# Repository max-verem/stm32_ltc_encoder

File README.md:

# stm32_ltc_encoder

This device used for decoding/encoding LTC (EBU Linear timecode) from/to VTRs or other sources.

Decoded Output sent to CDC serial. Encoding control cli available on second CDC serial.

## schematic

## photo

## encoding/generating LTC

## decoding LTC

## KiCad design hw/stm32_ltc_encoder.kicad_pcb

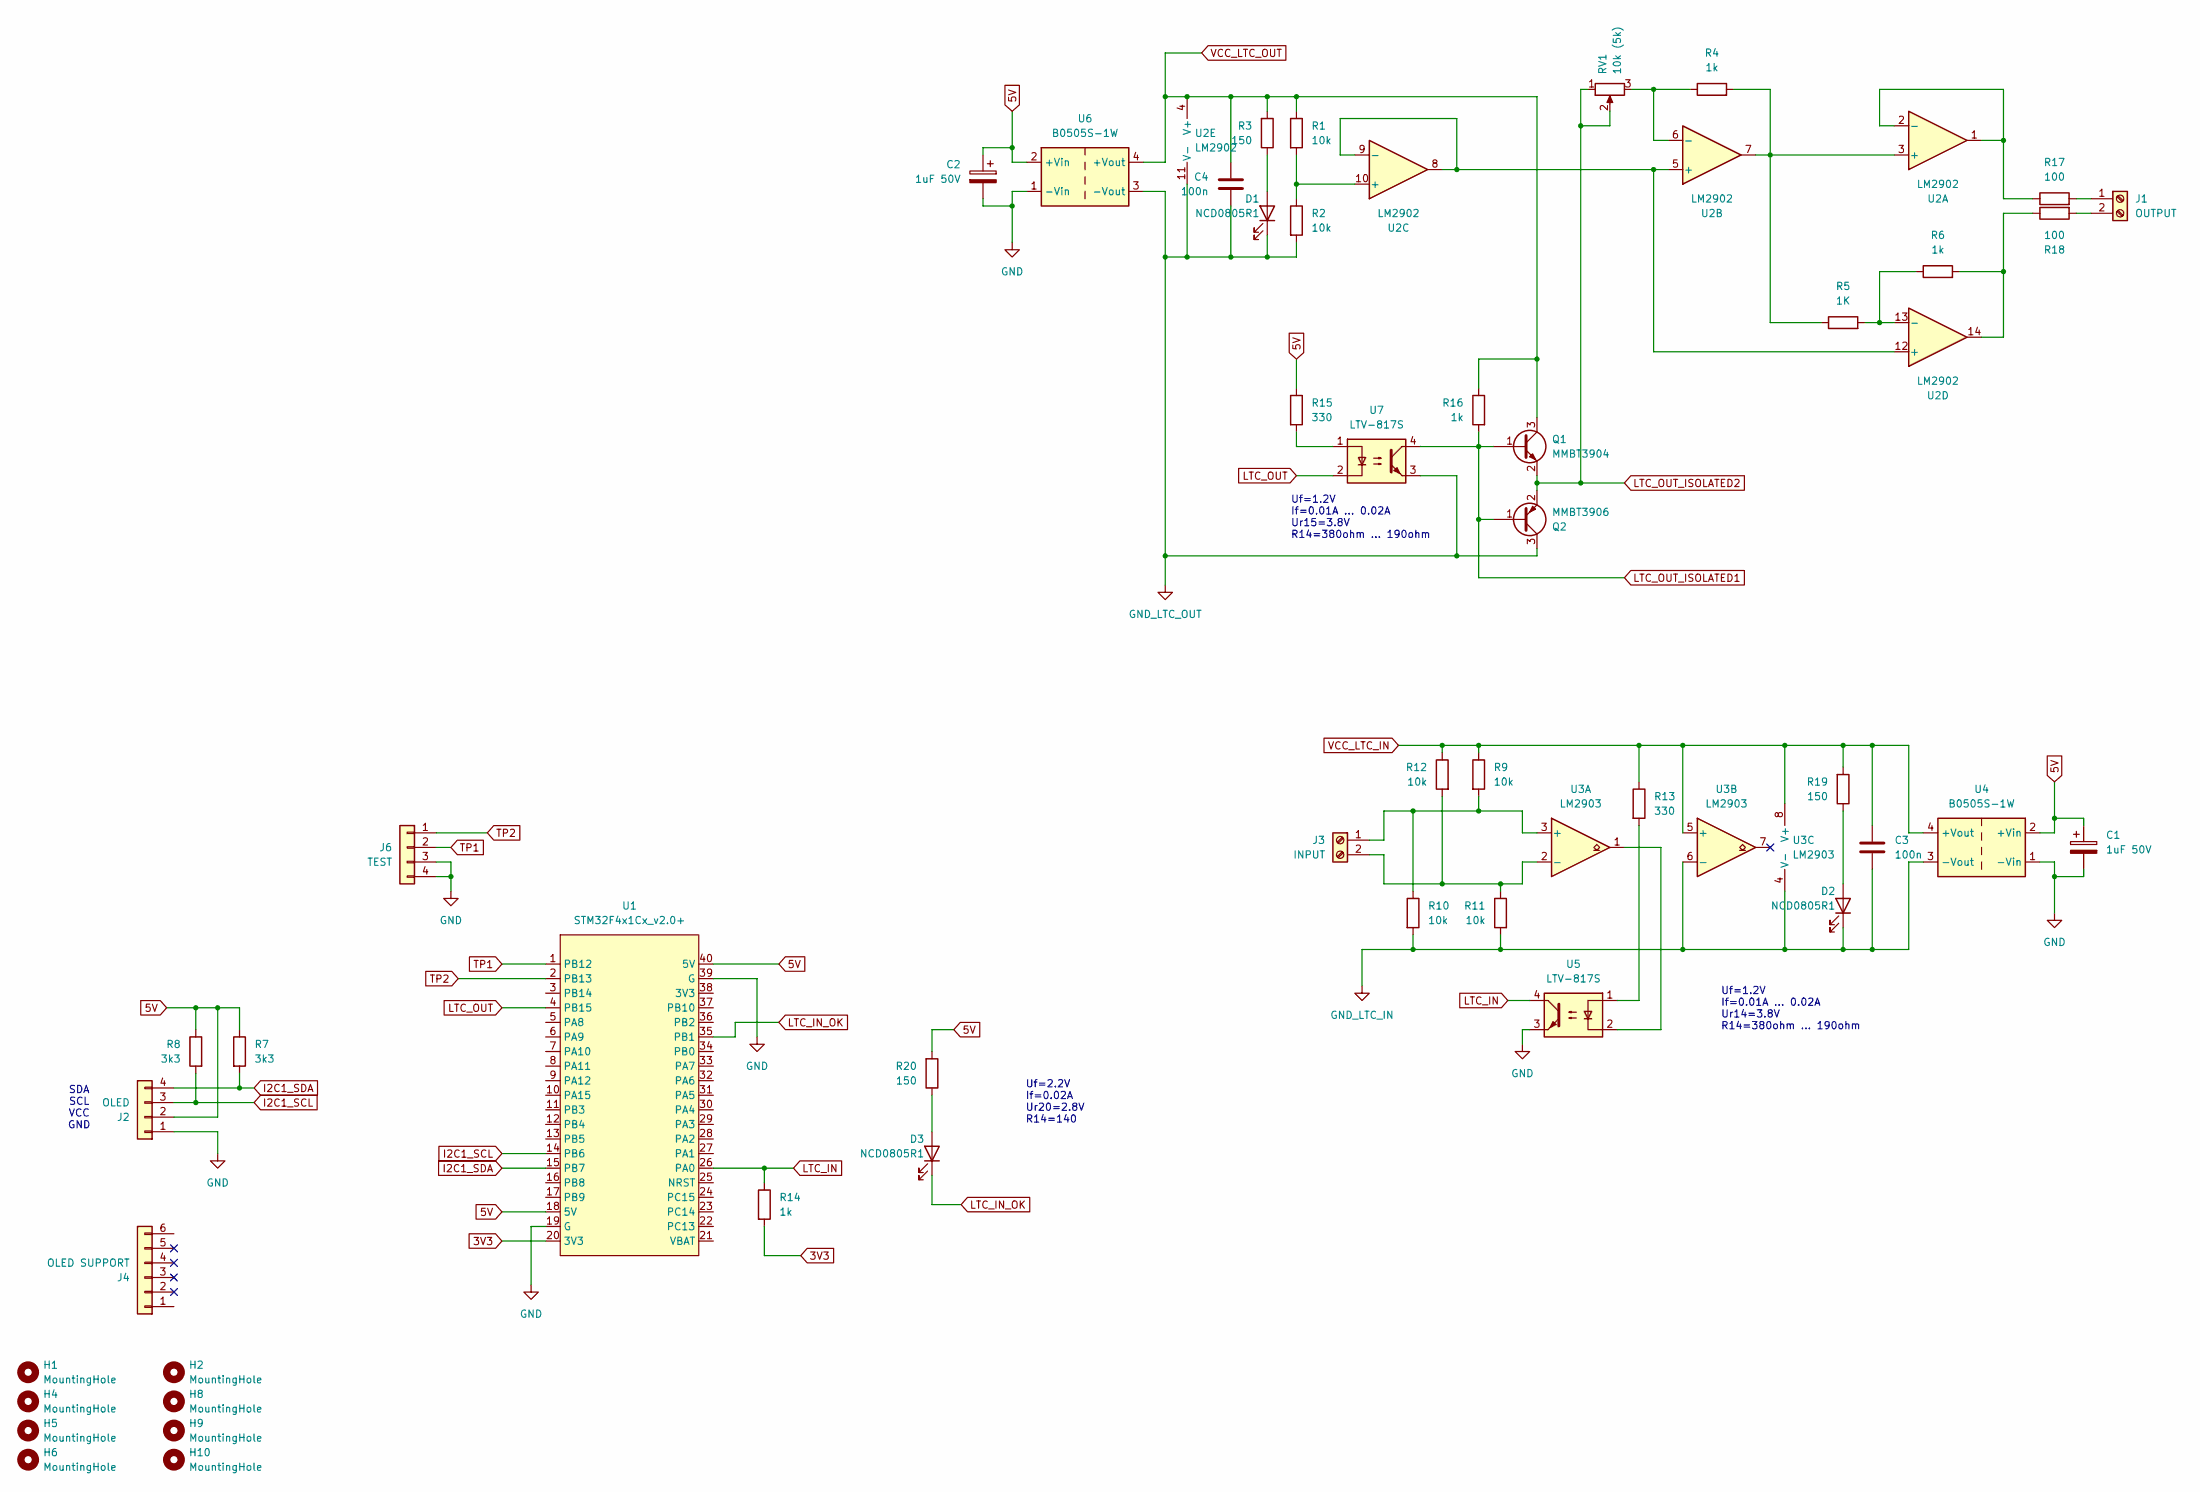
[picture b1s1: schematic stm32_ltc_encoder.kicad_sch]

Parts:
C1, C2: 1uF 50V; C_0805_2012Metric_Pad1.18x1.45mm_HandSolder
C3, C4: 100n; C_0805_2012Metric_Pad1.18x1.45mm_HandSolder
D1, D2, D3: NCD0805R1; LED_0805_2012Metric; JLCPCB Part # C84256
H1, H2, H4, H5, H6, H8, H9, H10: MountingHole; MountingHole_3.2mm_M3
J1: OUTPUT; TerminalBlock_bornier-2_P5.08mm; JLCPCB Part # C557646
J2: OLED; PinHeader_1x04_P2.54mm_Vertical
J3: INPUT; TerminalBlock_bornier-2_P5.08mm; JLCPCB Part # C557646
J4: OLED SUPPORT; PinHeader_1x06_P2.54mm_Vertical
J6: TEST; PinHeader_1x04_P2.54mm_Vertical
Q1: MMBT3904; SOT-23
Q2: MMBT3906; SOT-23
R1, R2, R9, R10, R11, R12: 10k; R_0805_2012Metric_Pad1.20x1.40mm_HandSolder
R3, R19, R20: 150; R_0805_2012Metric; JLCPCB Part # C17714
R4, R6, R14, R16: 1k; R_0805_2012Metric_Pad1.20x1.40mm_HandSolder
R5: 1K; R_0805_2012Metric_Pad1.20x1.40mm_HandSolder
R7, R8: 3k3; R_0805_2012Metric_Pad1.20x1.40mm_HandSolder
R13, R15: 330; R_0805_2012Metric_Pad1.20x1.40mm_HandSolder
R17, R18: 100; R_0805_2012Metric_Pad1.20x1.40mm_HandSolder
RV1: 10k (5k); Potentiometer_Bourns_3266W_Vertical
U1: STM32F4x1Cx_v2.0+; DIP-40_W15.24mm_LongPads
U2: LM2902; SOIC-14_3.9x8.7mm_P1.27mm
U3: LM2903; SOIC-8_3.9x4.9mm_P1.27mm
U4, U6: B0505S-1W; Converter_DCDC_TRACO_TME_03xxS_05xxS_12xxS_Single_THT
U5, U7: LTV-817S; SMDIP-4_W9.53mm

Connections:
3V3: R14.2, U1.20 (3V3)
5V: C1.1, C2.1, J2.2, R7.1, R8.1, R15.1, R20.2, U1.18 (5V), U1.40 (5V), U4.2 (+Vin), U6.2 (+Vin)
GND: C1.2, C2.2, J2.1, J6.3, J6.4, U1.19 (G), U1.39 (G), U4.1 (-Vin), U5.3, U6.1 (-Vin)
GND_LTC_IN: C3.2, D2.1 (K), R10.2, R11.2, U3.4 (V-), U3.6 (-), U4.3 (-Vout)
GND_LTC_OUT: C4.2, D1.1 (K), Q2.3 (C), R2.2, U2.11 (V-), U6.3 (-Vout), U7.3
I2C1_SCL: J2.3, R8.2, U1.14 (PB6)
I2C1_SDA: J2.4, R7.2, U1.15 (PB7)
LTC_IN: R14.1, U1.26 (PA0), U5.4
LTC_IN_OK: D3.1 (K), U1.35 (PB1)
LTC_OUT: U1.4 (PB15), U7.2
LTC_OUT_ISOLATED1: Q1.1 (B), Q2.1 (B), R16.2, U7.4
LTC_OUT_ISOLATED2: Q1.2 (E), Q2.2 (E), RV1.1, RV1.2
unnamed: D1.2 (A), R3.1
unnamed: D2.2 (A), R19.1
unnamed: D3.2 (A), R20.1
unnamed: J1.1, R17.2
unnamed: J1.2, R18.2
unnamed: J3.1, R9.2, R10.1, U3.3 (+)
unnamed: J3.2, R11.1, R12.2, U3.2 (-)
unnamed: R13.2, U5.1
unnamed: R15.2, U7.1
unnamed: R6.2, R18.1, U2.14
unnamed: R4.2, R5.1, U2.3 (+), U2.7
unnamed: R17.1, U2.1, U2.2 (-)
unnamed: U2.5 (+), U2.8, U2.9 (-), U2.12 (+)
unnamed: R4.1, RV1.3, U2.6 (-)
unnamed: R1.2, R2.1, U2.10 (+)
unnamed: R5.2, R6.1, U2.13 (-)
unnamed: U3.1, U5.2
TP1: J6.2, U1.1 (PB12)
TP2: J6.1, U1.2 (PB13)
VCC_LTC_IN: C3.1, R9.1, R12.1, R13.1, R19.2, U3.5 (+), U3.8 (V+), U4.4 (+Vout)
VCC_LTC_OUT: C4.1, Q1.3 (C), R1.1, R3.2, R16.1, U2.4 (V+), U6.4 (+Vout)

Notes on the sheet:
SDA SCL VCC GND
Uf=2.2V If=0.02A Ur20=2.8V R14=140
Uf=1.2V If=0.01A ... 0.02A Ur15=3.8V R14=380ohm ... 190ohm
Uf=1.2V If=0.01A ... 0.02A Ur14=3.8V R14=380ohm ... 190ohm

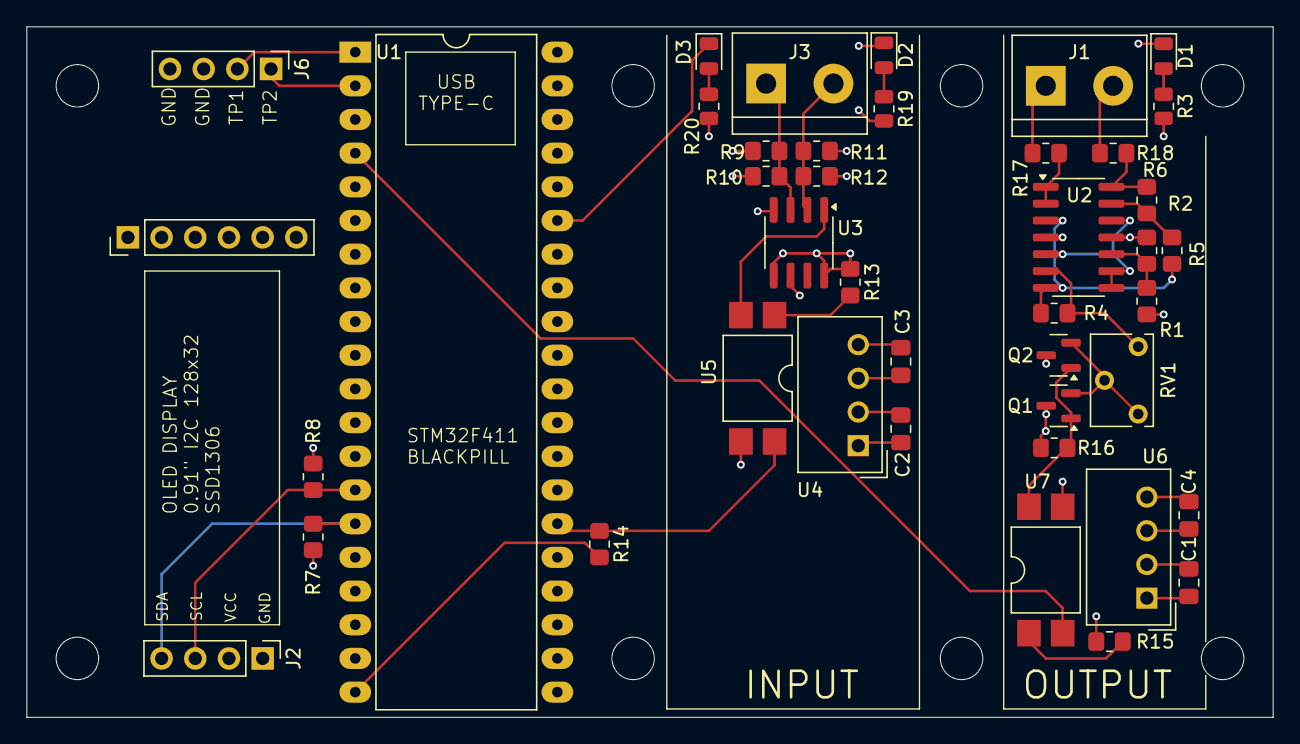
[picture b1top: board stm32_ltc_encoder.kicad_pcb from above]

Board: 4 copper layers, 94.0 x 52.1 mm, 50 parts (0 on the bottom side), 33 nets.

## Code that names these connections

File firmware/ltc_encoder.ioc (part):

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Mcu.Name=STM32F411C(C-E)Ux
Mcu.Package=UFQFPN48
Mcu.UserName=STM32F411CEUx
PA0-WKUP.GPIOParameters=GPIO_Speed,GPIO_PuPd
PA0-WKUP.GPIO_PuPd=GPIO_NOPULL
PA0-WKUP.GPIO_Speed=GPIO_SPEED_FREQ_VERY_HIGH
PA0-WKUP.Signal=S_TIM2_CH1_ETR
PA11.Mode=Device_Only
PA11.Signal=USB_OTG_FS_DM
PA12.Mode=Device_Only
PA12.Signal=USB_OTG_FS_DP
PA13.Mode=Serial_Wire
PA13.Signal=SYS_JTMS-SWDIO
PA14.Mode=Serial_Wire
PA14.Signal=SYS_JTCK-SWCLK
PA8.Mode=Activate_SOF_FS
PA8.Signal=USB_OTG_FS_SOF
PB1.GPIOParameters=GPIO_PuPd,GPIO_Label,GPIO_ModeDefaultOutputPP
PB1.GPIO_Label=LTC_IN_OK
PB1.GPIO_ModeDefaultOutputPP=GPIO_MODE_OUTPUT_OD
PB1.GPIO_PuPd=GPIO_NOPULL
PB1.Signal=GPIO_Output
PB12.GPIOParameters=GPIO_Speed,PinState,GPIO_Label
PB12.GPIO_Label=TP1
PB12.GPIO_Speed=GPIO_SPEED_FREQ_VERY_HIGH
PB12.PinState=GPIO_PIN_RESET
PB12.Signal=GPIO_Output
PB13.GPIOParameters=GPIO_Speed,GPIO_Label
PB13.GPIO_Label=TP2
PB13.GPIO_Speed=GPIO_SPEED_FREQ_VERY_HIGH
PB13.Signal=GPIO_Output
PB15.GPIOParameters=GPIO_Speed,GPIO_PuPd,GPIO_Label,GPIO_ModeDefaultOutputPP
PB15.GPIO_Label=LTC_OUT
PB15.GPIO_ModeDefaultOutputPP=GPIO_MODE_OUTPUT_OD
PB15.GPIO_PuPd=GPIO_NOPULL
PB15.GPIO_Speed=GPIO_SPEED_FREQ_VERY_HIGH
PB15.Signal=GPIO_Output
PB6.Mode=I2C
PB6.Signal=I2C1_SCL
PB7.Mode=I2C
PB7.Signal=I2C1_SDA
PC13-ANTI_TAMP.GPIOParameters=GPIO_PuPd,GPIO_Label,GPIO_ModeDefaultOutputPP
PC13-ANTI_TAMP.GPIO_Label=LED
PC13-ANTI_TAMP.GPIO_ModeDefaultOutputPP=GPIO_MODE_OUTPUT_OD
PC13-ANTI_TAMP.GPIO_PuPd=GPIO_NOPULL
PC13-ANTI_TAMP.Signal=GPIO_Output
PC14-OSC32_IN.Mode=LSE-External-Oscillator
PC14-OSC32_IN.Signal=RCC_OSC32_IN
PC15-OSC32_OUT.Mode=LSE-External-Oscillator
PC15-OSC32_OUT.Signal=RCC_OSC32_OUT
PH0\ -\ OSC_IN.Mode=HSE-External-Oscillator
PH0\ -\ OSC_IN.Signal=RCC_OSC_IN
PH1\ -\ OSC_OUT.Mode=HSE-External-Oscillator
PH1\ -\ OSC_OUT.Signal=RCC_OSC_OUT
RCC.HSE_VALUE=25000000
RCC.SYSCLKFreq_VALUE=48000000
RCC.SYSCLKSource=RCC_SYSCLKSOURCE_PLLCLK
board=custom

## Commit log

2025-03-06 Initial load
2025-03-06 Split out ltc encoding code out of main.c
2025-03-06 Main.c code cleanup
2025-03-08 Re-implement bit sequence output with GPIO rather then I2S
2025-03-08 Rename functions to match real functionality
2025-03-08 Integrate LTC decoder
2025-03-09 Add oled display support. Use AL94_USB_Composite composite device implementation
2025-03-09 Rework displaying IN/OUT timecodes
2025-03-09 Add padding to framebuffer bank/row/line
2025-03-17 Main HW schematic/pcb added
2025-03-17 Add some docs
2025-04-13 Finalize release
2025-04-13 Added photos and images
